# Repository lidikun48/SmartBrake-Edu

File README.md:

# SmartBrake Edu

SmartBrake Edu adalah prototipe sistem telemetri pengereman berbasis ESP32 yang dikembangkan untuk membantu observasi praktik pengereman sepeda motor pada pelatihan *safety riding*. Sistem memperoleh data tekanan rem depan dan belakang dalam bentuk persentase relatif, membaca kecepatan roda depan dan belakang, menghitung distribusi penggunaan rem F:R, serta menampilkan dan merekam data melalui Web Dashboard pada jaringan Wi-Fi lokal.

Repository ini digunakan sebagai dokumentasi teknis source code dan desain perangkat keras SmartBrake Edu.

## Fitur Utama

- Pembacaan tekanan rem depan dan belakang dalam skala relatif 0–100%.
- Kalibrasi relatif menggunakan metode **Set Zero–Set Max**.
- Pembacaan kecepatan roda depan dan belakang menggunakan sensor *magnetic pickup*.
- Perhitungan distribusi penggunaan rem depan dan belakang (F:R).
- ESP32 sebagai *local access point* dan Web Server.
- Web Dashboard responsif untuk smartphone, tablet, dan laptop.
- Data Logger berbasis browser.
- Brake Test History dan Session Manager.
- Grafik kecepatan dan tekanan selama sesi.
- Brake Event Timeline dan Distribution History.
- Ekspor data hasil sesi.
- Penyimpanan konfigurasi perangkat menggunakan Preferences/NVS.
- Pembaruan firmware melalui OTA.

## Arsitektur Singkat

```text
Sensor Tekanan Depan & Belakang
            |
            v
       Pembacaan ADC
            |
            v
         Filter EMA
            |
            v
   Kalibrasi Relatif
     Set Zero–Set Max
            |
            v
 Persentase Tekanan 0–100%
            |
            +----------------------+
                                   |
Sensor Magnetic Pickup F/R        |
            |                      |
            v                      |
      Pembacaan Pulsa              |
            |                      |
            v                      |
 Perhitungan Kecepatan             |
            |                      |
            +----------+-----------+
                       |
                       v
                     ESP32
                       |
                       v
              Wi-Fi Lokal / HTTP
                       |
                       v
                 Web Dashboard
                       |
                       v
                  Data Logger
```

## Perangkat Keras Utama

- ESP32 DevKit V1
- 2 sensor tekanan hidrolik
- 2 sensor *magnetic pickup*
- PC817 pada antarmuka sensor kecepatan
- rangkaian pengondisi sinyal analog
- LED indikator sistem dan sensor
- sistem catu daya portabel

## Konfigurasi GPIO

| Fungsi | GPIO |
|---|---:|
| Sensor tekanan depan | 32 |
| Sensor tekanan belakang | 33 |
| Sensor kecepatan roda depan | 26 |
| Sensor kecepatan roda belakang | 27 |
| LED system | 2 |
| LED tekanan depan | 5 |
| LED tekanan belakang | 19 |
| LED kecepatan depan | 3 |
| LED kecepatan belakang | 22 |

## Struktur Repository

```text
SmartBrake-Edu/
├── README.md
├── platformio.ini
├── .gitignore
├── src/
│   └── main.cpp
├── docs/
│   ├── hardware/
│   │   └── README.md
│   ├── schematic/
│   │   ├── BrakePressure4.kicad_pro
│   │   ├── BrakePressure4.kicad_sch
│   │   ├── BrakePressure4.kicad_pcb
│   │   └── README.md
│   └── screenshots/
│       └── README.md
└── data/
    └── README.md
```

## Source Code

Firmware utama dan Web Dashboard berada pada:

```text
src/main.cpp
```

Web Dashboard disimpan di dalam firmware menggunakan `PROGMEM`, sehingga HTML, CSS, dan JavaScript berada pada file source yang sama dengan program ESP32.

## Pengembangan dengan PlatformIO

Project menggunakan framework Arduino pada PlatformIO untuk board ESP32 DevKit V1.

Build firmware:

```bash
pio run
```

Konfigurasi build dan metode upload terdapat pada `platformio.ini`.

### Upload USB

Untuk upload melalui kabel USB, gunakan `upload_protocol = esptool` pada `platformio.ini`.

### Upload OTA

Konfigurasi repository menyediakan pengaturan OTA menggunakan `espota` pada alamat lokal perangkat. Pastikan komputer telah terhubung ke jaringan SmartBrake Edu sebelum melakukan upload OTA.

## Konfigurasi Wi-Fi

Demi keamanan repository publik, password Access Point pada `src/main.cpp` menggunakan placeholder:

```cpp
const char* AP_PASS = "CHANGE_ME";
```

Ganti nilai tersebut dengan password yang akan digunakan pada perangkat sebelum melakukan build untuk penggunaan aktual. Jangan menyimpan password pribadi atau kredensial sensitif di repository publik.

## Desain KiCad

Berkas proyek KiCad tersedia pada folder [`docs/schematic`](docs/schematic):

- `BrakePressure4.kicad_sch`
- `BrakePressure4.kicad_pcb`
- `BrakePressure4.kicad_pro`

## Catatan Pengukuran

Nilai tekanan yang ditampilkan SmartBrake Edu merupakan **persentase tekanan relatif** berdasarkan kalibrasi Set Zero–Set Max. Sistem tidak dikalibrasi sebagai instrumen pengukuran tekanan absolut dalam satuan PSI, bar, atau MPa dan tidak mengukur gaya pengereman aktual pada bidang kontak ban dengan permukaan jalan.

Parameter kecepatan digunakan sebagai data pendukung untuk mengamati perubahan laju selama sesi dan tidak dinyatakan sebagai hasil pengukuran kecepatan terkalibrasi terhadap instrumen referensi.

## Konteks Akademik

SmartBrake Edu dikembangkan dalam Proyek Akhir Program Studi D4 Teknik Mesin Otomotif, Fakultas Vokasi, Universitas Negeri Yogyakarta.

**Pengembang:** Chiko Casillas  
**Tahun:** 2026

## Status Repository

- Firmware utama: tersedia.
- Web Dashboard: terintegrasi pada firmware.
- Skematik KiCad: tersedia.
- Layout PCB KiCad: tersedia.
- Konfigurasi PlatformIO: tersedia.
- Folder data dan dokumentasi tambahan: disiapkan untuk contoh data serta dokumentasi akademik yang dapat dipublikasikan.

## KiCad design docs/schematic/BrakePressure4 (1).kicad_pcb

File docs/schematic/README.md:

# KiCad Hardware Design

Folder ini memuat berkas desain perangkat keras SmartBrake Edu yang digunakan untuk dokumentasi proyek.

## Berkas

- `BrakePressure4.kicad_sch` — skematik rangkaian SmartBrake Edu.
- `BrakePressure4.kicad_pcb` — layout PCB SmartBrake Edu.
- `BrakePressure4.kicad_pro` — berkas proyek KiCad.

Berkas preferensi lokal KiCad (`*.kicad_prl`) tidak disertakan karena tidak diperlukan untuk membuka atau meninjau desain utama.

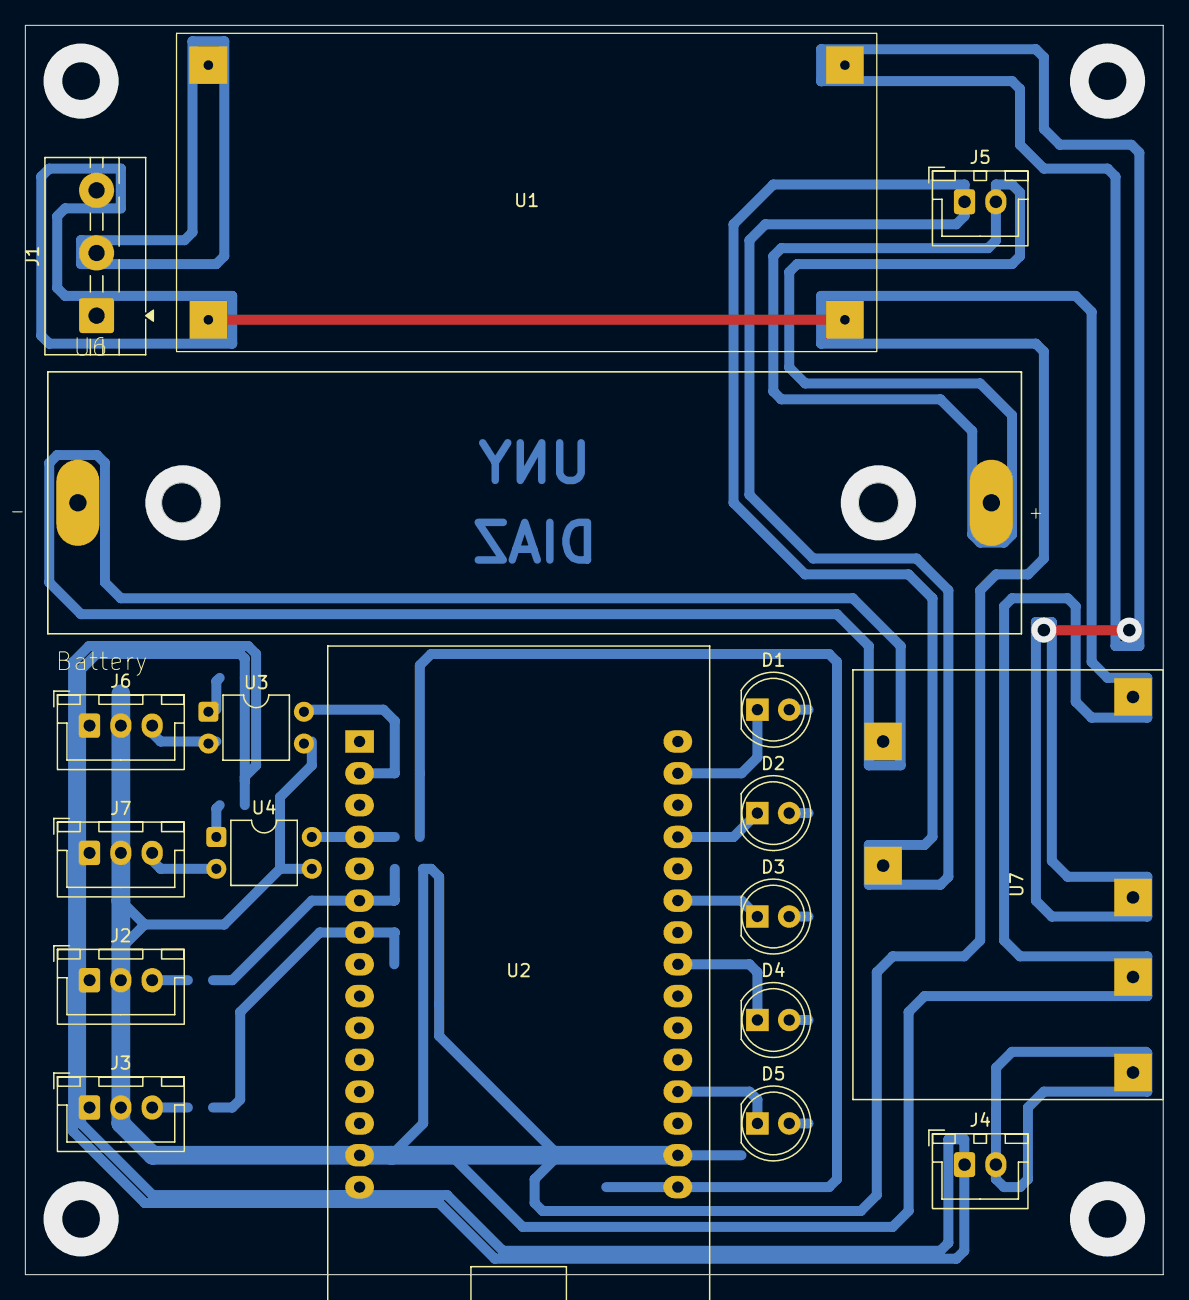
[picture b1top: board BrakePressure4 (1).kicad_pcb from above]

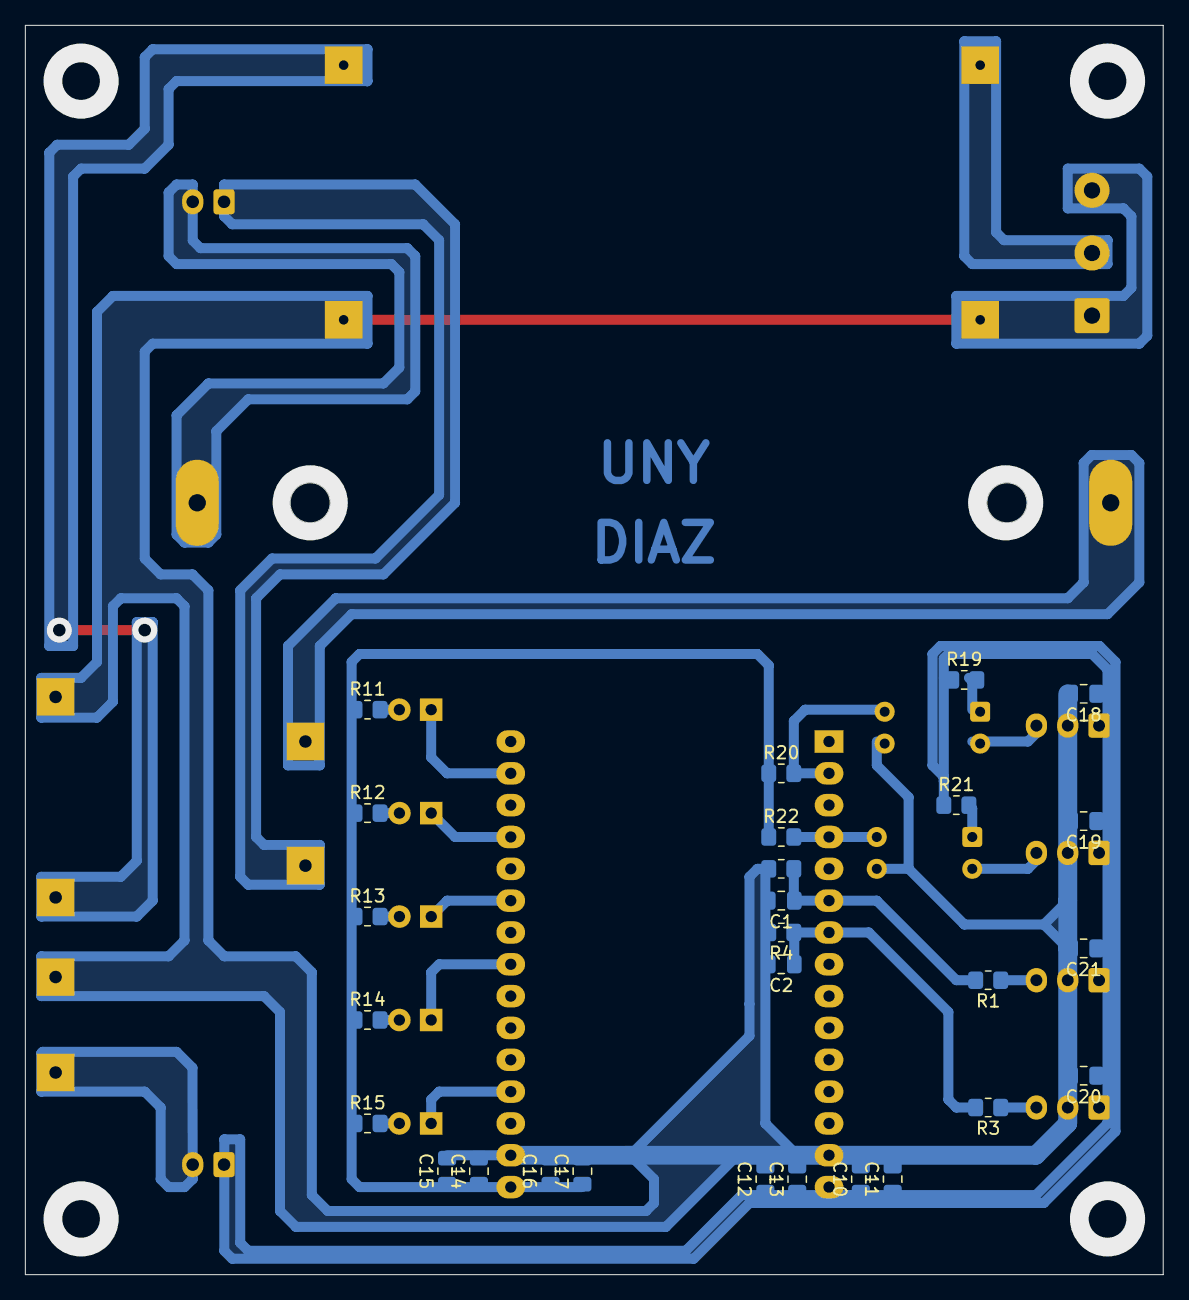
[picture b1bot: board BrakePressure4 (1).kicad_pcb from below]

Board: 2 copper layers, 90.8 x 99.7 mm, 45 parts (27 on the bottom side), 29 nets.

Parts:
C1, C2, C10, C11, C12, C13, C14, C15, C16, C17, C18, C19, C20, C21: 1uF; C_0805_2012Metric_Pad1.18x1.45mm_HandSolder
D1, D2, D3, D4, D5: LED; LED_D5.0mm_Clear
J1: PWR; TerminalBlock_MaiXu_MX126-5.0-03P_1x03_P5.00mm
J2: SEN1; JST_XH_B3B-XH-A_1x03_P2.50mm_Vertical
J3, J6, J7: SEN2; JST_XH_B3B-XH-A_1x03_P2.50mm_Vertical
J4, J5: Switch; JST_XH_B2B-XH-A_1x02_P2.50mm_Vertical
R1, R3: 4,7k; R_0805_2012Metric_Pad1.20x1.40mm_HandSolder
R2, R4, R19, R21: 10k; R_0805_2012Metric_Pad1.20x1.40mm_HandSolder
R11, R12, R13, R14, R15: 220; R_0805_2012Metric_Pad1.20x1.40mm_HandSolder
R20, R22: 1k; R_0805_2012Metric_Pad1.20x1.40mm_HandSolder
U1: XL4015_Module; XL4015
U2: ESP32_Dev
U3, U4: PC817; DIP-4_W7.62mm
U6: Battery; BAT_BH-18650-PC
U7: Battery_Charger_TP4056; Module_TP4056

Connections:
+3V3: C14.1, C15.1, C16.1, C17.1, R11.1, R12.1, R13.1, R14.1, R15.1, R20.1, R22.1, U2.16 (3v3)
+12V: J1.2, U1.1 (In+)
GND: C1.2, C2.2, C10.2, C11.2, C12.2, C13.2, C14.2, C15.2, C16.2, C17.2, C18.2, C19.2, C20.2, C21.2, J1.1, J1.3, J2.2, J3.2, J6.2, J7.2, R2.2, R4.2, U1.2 (In-), U1.4 (Out-), U2.14 (GND), U2.17 (GND), U3.3, U4.3, U7.2 (OUT-), U7.4 (IN-)
IDO1: D1.1 (K), U2.29 (SCL/IO22)
IDO2: D2.1 (K), U2.27 (RXD/IO3)
IDO3: D3.1 (K), U2.25 (MISO/IO19)
IDO4: D4.1 (K), U2.23 (IO5)
IDON: D5.1 (K), U2.19 (IO2/ADC2_2)
unnamed: D1.2 (A), R11.2
unnamed: D2.2 (A), R12.2
unnamed: D3.2 (A), R13.2
unnamed: D4.2 (A), R14.2
unnamed: D5.2 (A), R15.2
unnamed: J4.2, U7.1 (OUT+)
unnamed: J5.1, U7.5 (B+)
unnamed: J5.2, U6.P
unnamed: J6.3, U3.2
unnamed: J7.3, U4.2
unnamed: R19.2, U3.1
unnamed: R21.2, U4.1
unnamed: U1.3 (Out+), U7.3 (IN+)
unnamed: U6.N, U7.6 (B-)
P_IN1: C1.1, R1.2, R2.1, U2.6 (IO32/ADC1_4)
P_IN2: C2.1, R3.2, R4.1, U2.7 (IP33/ADC1_5)
P_IN3: R20.2, U2.2 (IO36/ADC1_0), U3.4
P_IN4: R22.2, U2.4 (IO34/ADC1_6), U4.4
S_IN1: J2.3, R1.1
S_IN2: J3.3, R3.1
VCC: C10.1, C11.1, C12.1, C13.1, C18.1, C19.1, C20.1, C21.1, J2.1, J3.1, J4.1, J6.1, J7.1, R19.1, R21.1, U2.15 (VIN)
